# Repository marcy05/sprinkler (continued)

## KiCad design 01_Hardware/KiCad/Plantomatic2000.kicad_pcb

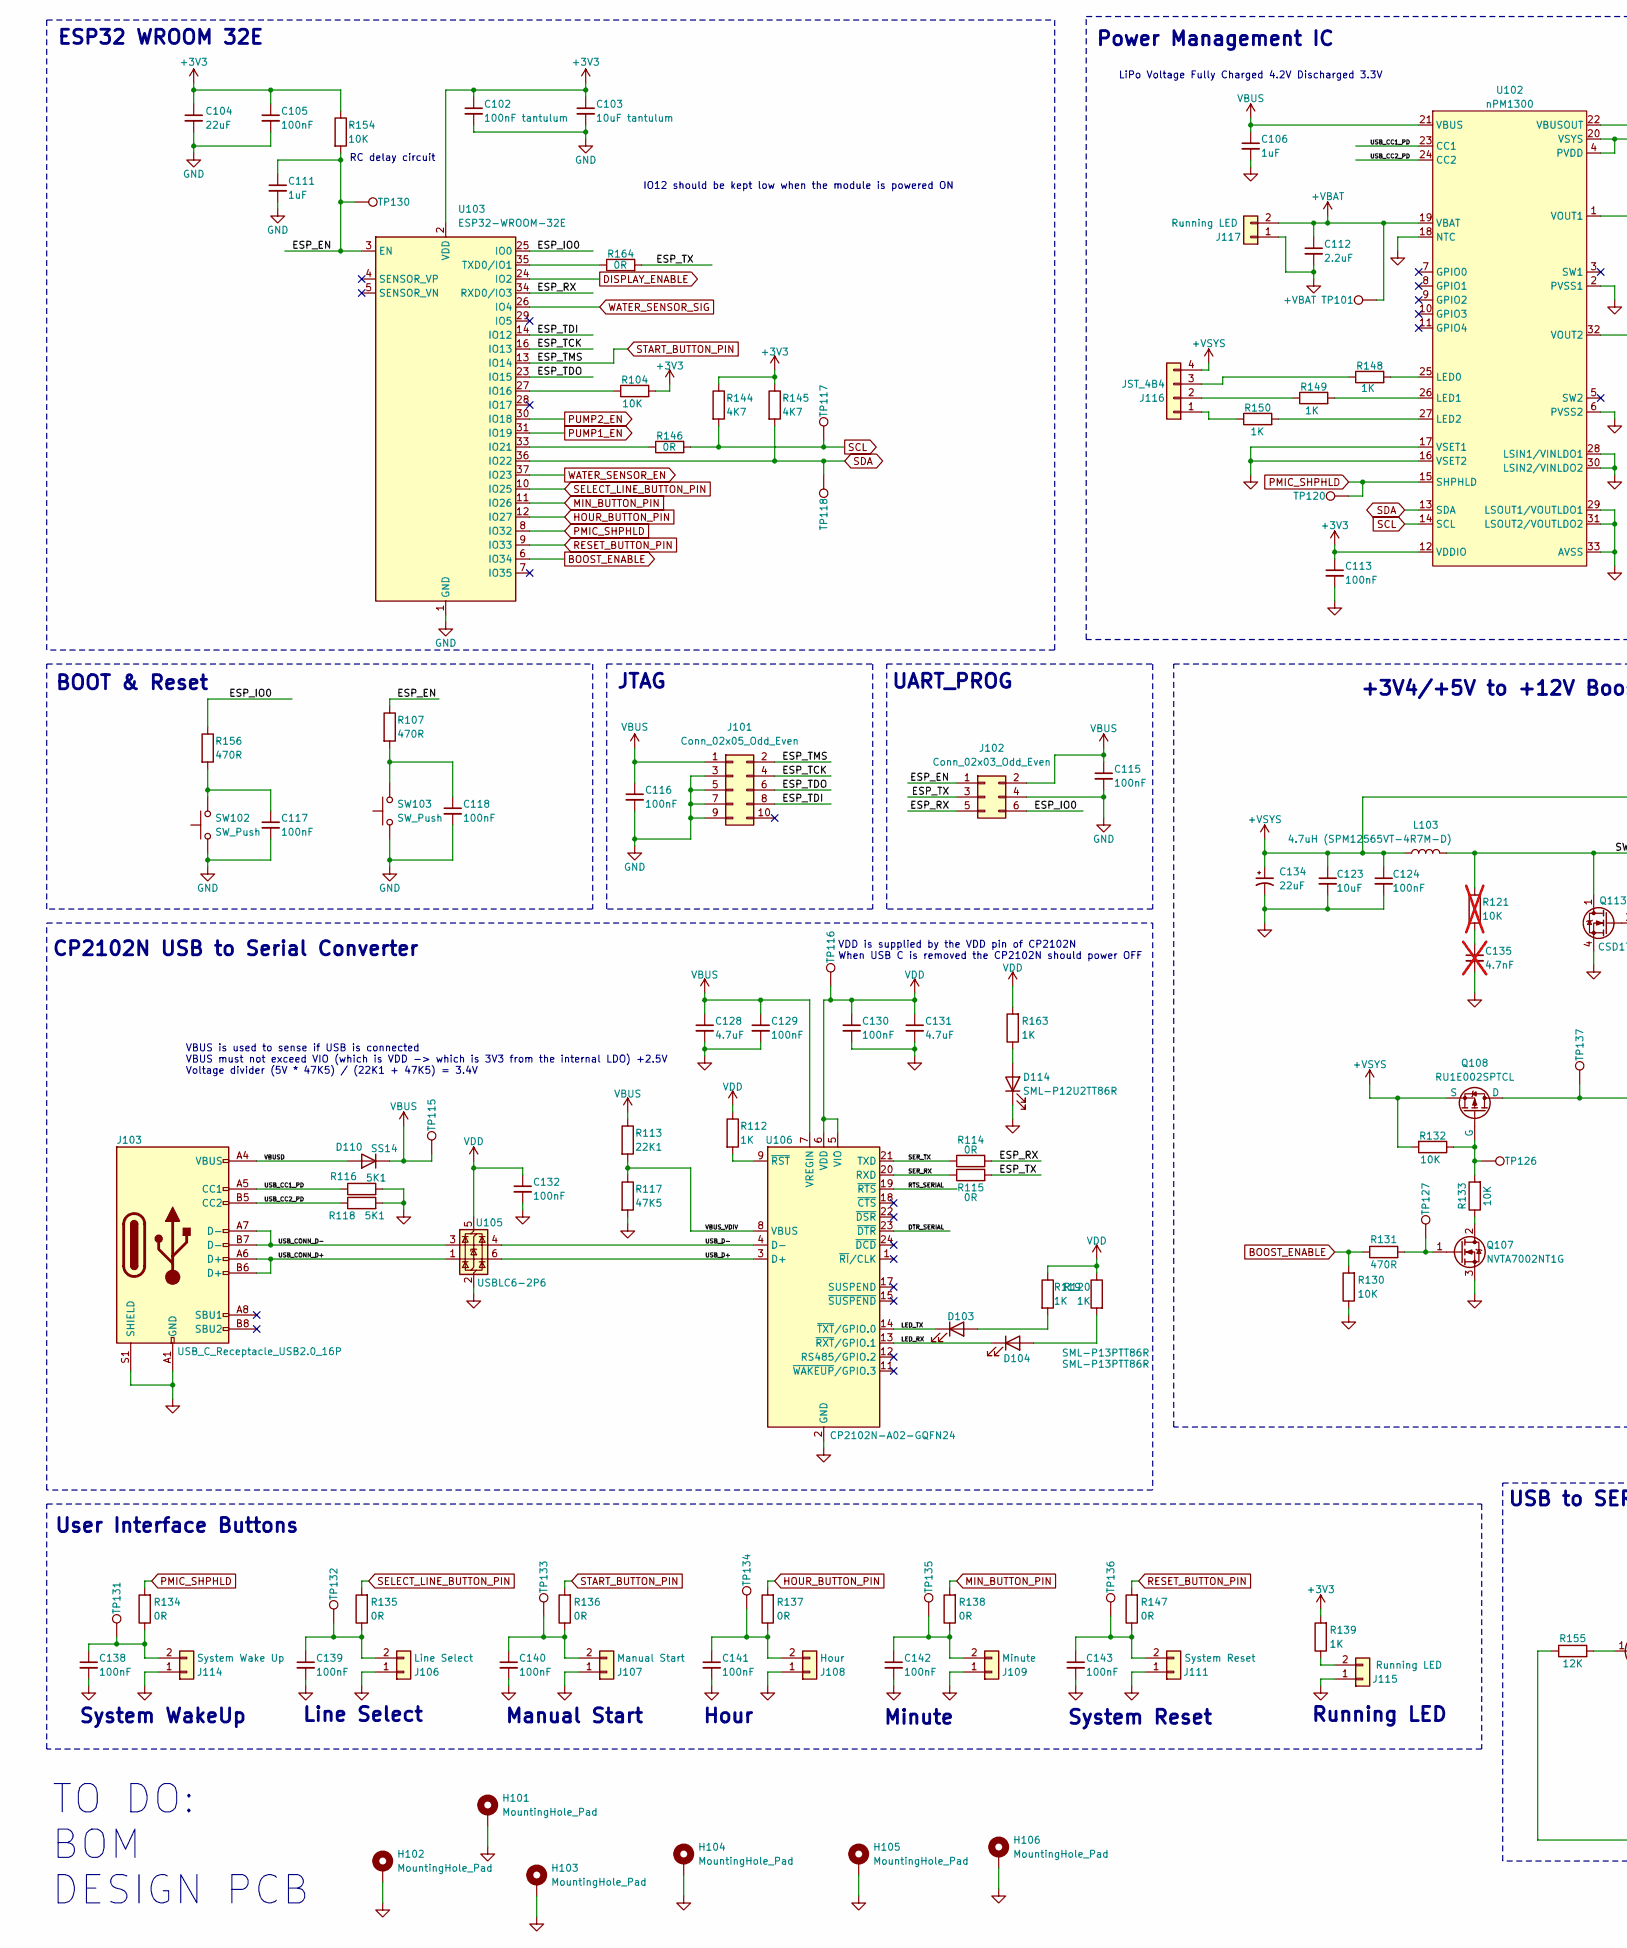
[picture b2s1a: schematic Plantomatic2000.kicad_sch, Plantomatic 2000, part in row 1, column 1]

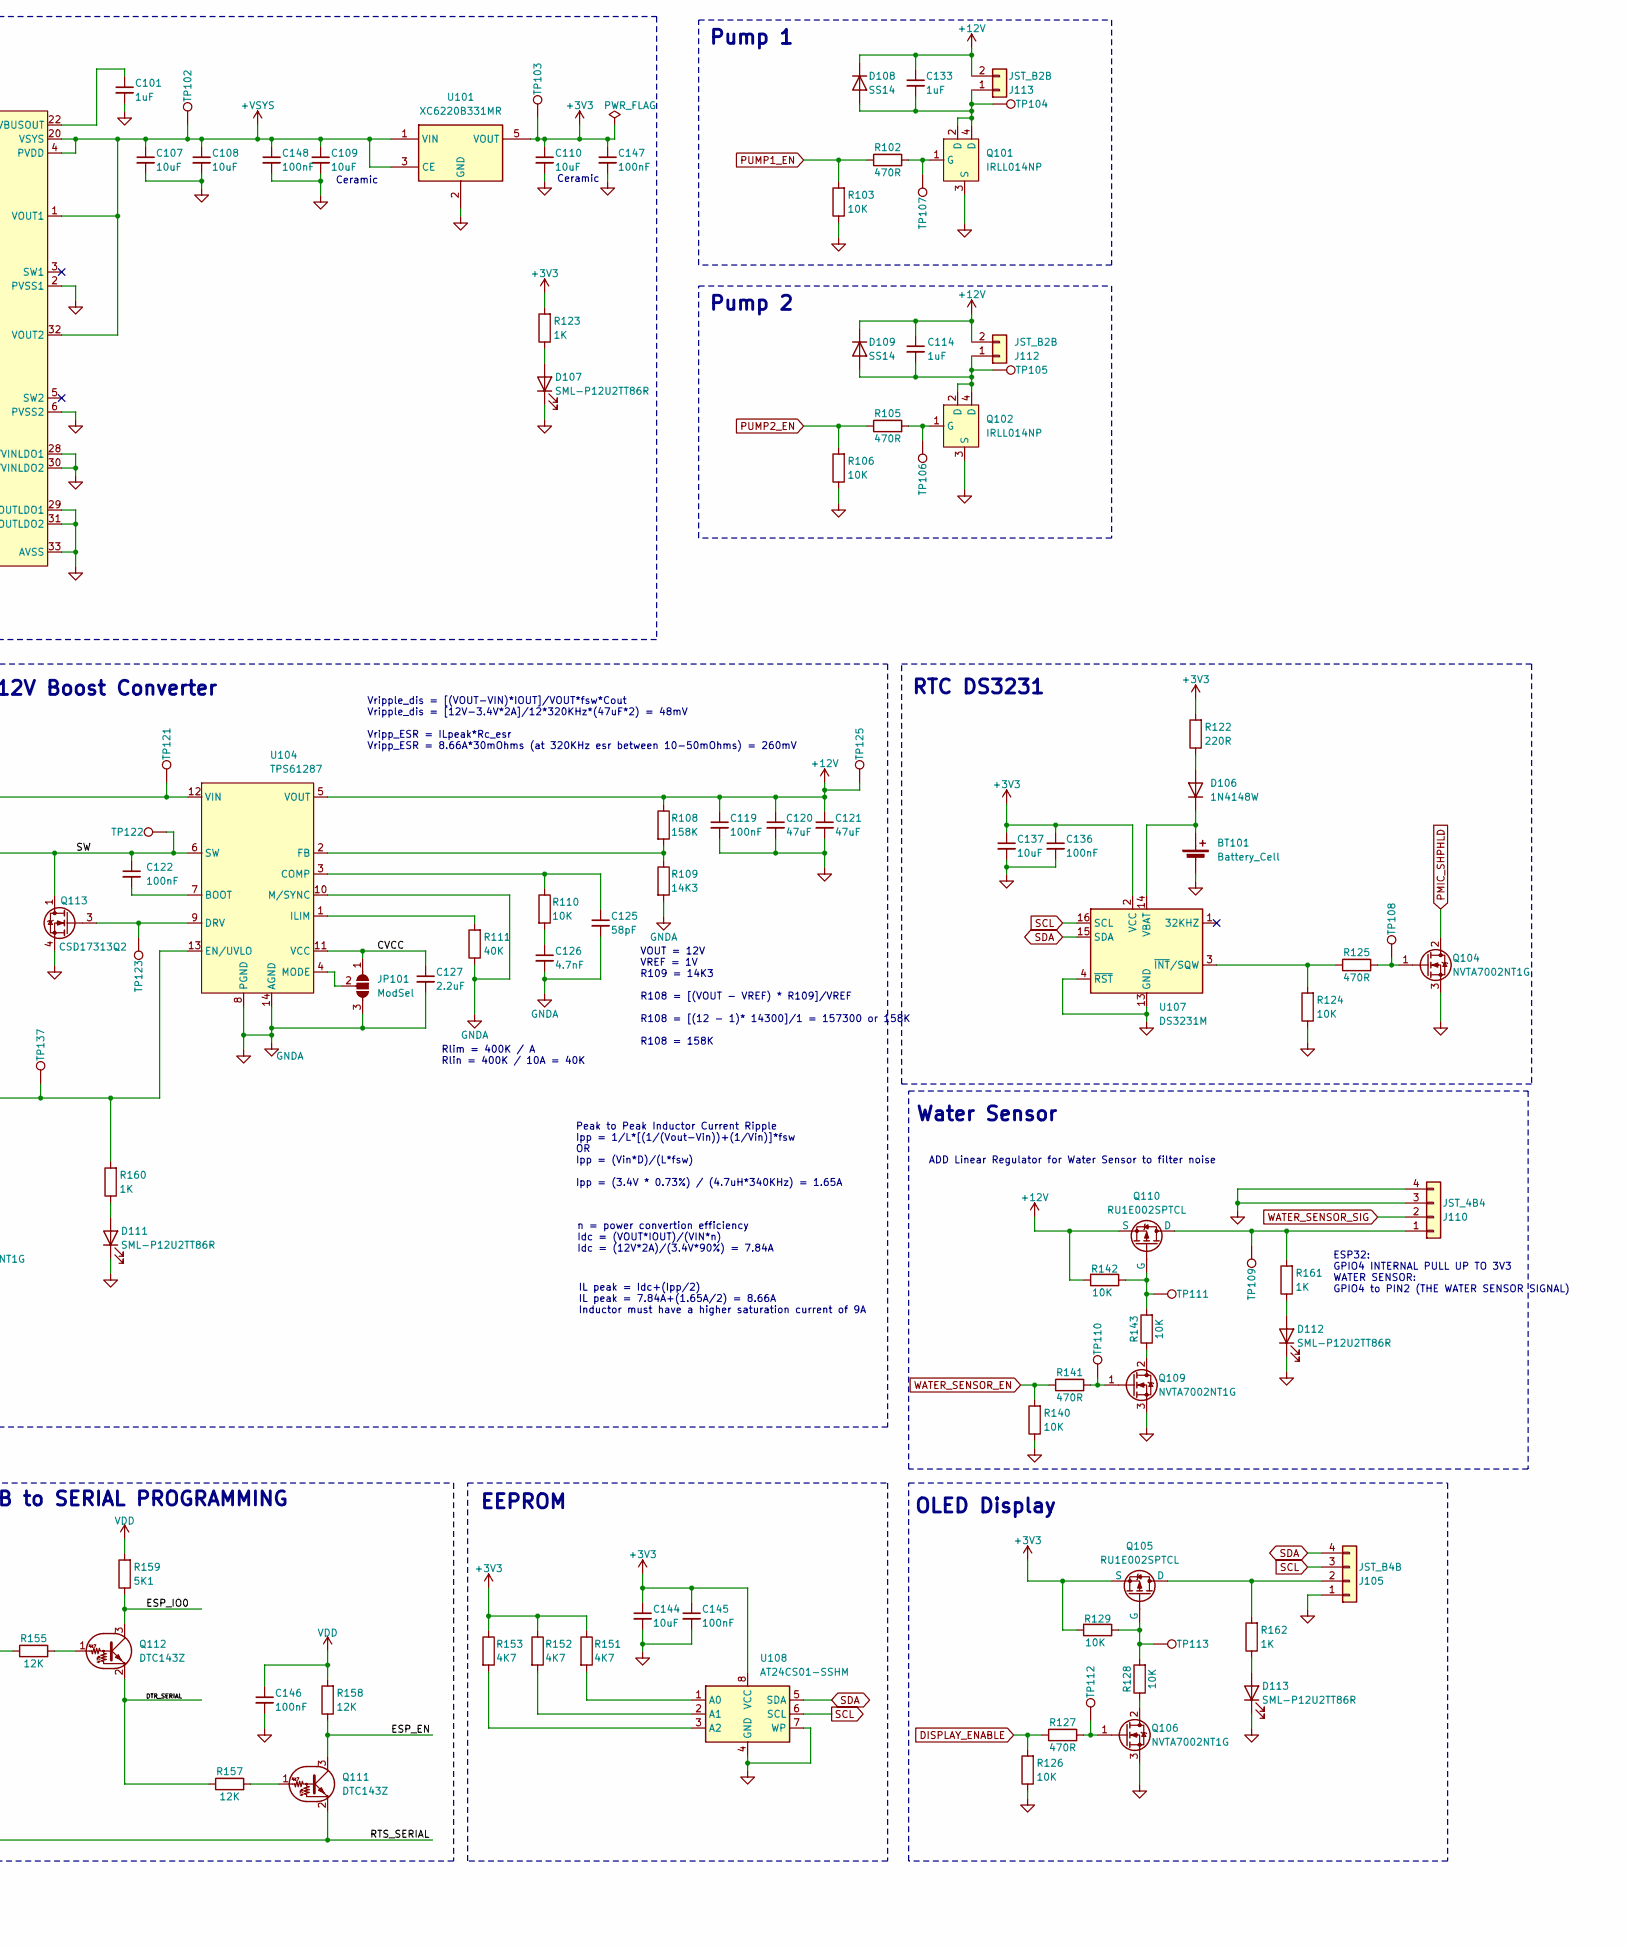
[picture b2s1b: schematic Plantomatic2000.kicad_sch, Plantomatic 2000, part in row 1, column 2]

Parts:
BT101: Battery_Cell; BatteryHolder_MYOUNG_BS-07-A1BJ001_CR2032
C101, C106, C111: 1uF; C_0402_1005Metric
C102: 100nF tantulum; C_1206_3216Metric
C103: 10uF tantulum; C_1206_3216Metric
C104, C134: 22uF; C_0603_1608Metric
C105, C113, C115, C116, C117, C118, C119, C122, C124, C129, C130, C132, C136, C138, C139, C140, C141, C142, C143, C145, C146, C147, C148: 100nF; C_0402_1005Metric
C107, C108, C137, C144: 10uF; C_0402_1005Metric
C109, C110, C123: 10uF; C_0603_1608Metric
C112: 2.2uF; C_0402_1005Metric
C114, C133: 1uF; C_0603_1608Metric
C120, C121: 47uF; C_0603_1608Metric
C125: 58pF; C_0402_1005Metric
C126: 4.7nF; C_0402_1005Metric
C127: 2.2uF; C_0603_1608Metric
C128, C131: 4.7uF; C_0603_1608Metric
C135: 4.7nF; C_0402_1005Metric; not fitted
D103, D104: SML-P13PTT86R; LED_0402_1005Metric
D106: 1N4148W; D_SOD-123
D107, D111, D112, D113, D114: SML-P12U2TT86R; LED_0402_1005Metric
D108, D109, D110: SS14; SS14M_Flyback_Diode
H101, H102, H103, H104, H105, H106: MountingHole_Pad; MountingHole_2.2mm_M2_Pad_TopBottom
J101: Conn_02x05_Odd_Even; PinHeader_2x05_P1.27mm_Vertical_SMD
J102: Conn_02x03_Odd_Even; PinHeader_2x03_P1.27mm_Vertical_SMD
J103: USB_C_Receptacle_USB2.0_16P; USB_C_Receptacle_Palconn_UTC16-G
J105: JST_B4B; JST_EH_B4B-EH-A_1x04_P2.50mm_Vertical
J106: Line Select; JST_EH_B2B-EH-A_1x02_P2.50mm_Vertical
J107: Manual Start; JST_EH_B2B-EH-A_1x02_P2.50mm_Vertical
J108: Hour; JST_EH_B2B-EH-A_1x02_P2.50mm_Vertical
J109: Minute; JST_EH_B2B-EH-A_1x02_P2.50mm_Vertical
J110, J116: JST_4B4; JST_EH_B4B-EH-A_1x04_P2.50mm_Vertical
J111: System Reset; JST_EH_B2B-EH-A_1x02_P2.50mm_Vertical
J112, J113: JST_B2B; JST_EH_B2B-EH-A_1x02_P2.50mm_Vertical
J114: System Wake Up; JST_EH_B2B-EH-A_1x02_P2.50mm_Vertical
J115, J117: Running LED; JST_EH_B2B-EH-A_1x02_P2.50mm_Vertical
JP101: ModSel; SolderJumper-3_P1.3mm_Open_RoundedPad1.0x1.5mm
L103: 4.7uH (SPM12565VT-4R7M-D); SPM12565VT-4R7M
Q101, Q102: IRLL014NP; SOT-223
Q104, Q106, Q107, Q109: NVTA7002NT1G; SOT-323_SC-70
Q105, Q108, Q110: RU1E002SPTCL; SOT-323_SC-70
Q111, Q112: DTC143Z; SOT-23-3
Q113: CSD17313Q2; Texas_DQK
R102, R105, R107, R125, R127, R131, R141, R156: 470R; R_0402_1005Metric
R103, R104, R106, R110, R124, R126, R128, R129, R130, R132, R133, R140, R142, R143, R154: 10K; R_0402_1005Metric
R108: 158K; R_0402_1005Metric
R109: 14K3; R_0402_1005Metric
R111: 40K; R_0402_1005Metric
R112, R119, R120, R123, R139, R148, R149, R150, R160, R161, R162, R163: 1K; R_0402_1005Metric
R113: 22K1; R_0402_1005Metric
R114, R115, R134, R135, R136, R137, R138, R146, R147, R164: 0R; R_0402_1005Metric
R116, R118, R159: 5K1; R_0402_1005Metric
R117: 47K5; R_0402_1005Metric
R121: 10K; R_0402_1005Metric; not fitted
R122: 220R; R_0402_1005Metric
R144, R145, R151, R152, R153: 4K7; R_0402_1005Metric
R155, R157, R158: 12K; R_0402_1005Metric
SW102, SW103: SW_Push; SW_SPST_PTS645
TP101: +VBAT; TestPoint_Pad_D1.0mm
TP102, TP103, TP104, TP105, TP106, TP107, TP108, TP109, TP110, TP111, TP112, TP113, TP115, TP116, TP117, TP118, TP120, TP121, TP122, TP123, TP125, TP126, TP127, TP130, TP131, TP132, TP133, TP134, TP135, TP136, TP137: TestPoint_Pad_D1.0mm
U101: XC6220B331MR; SOT-23-5
U102: nPM1300; QFN-32-1EP_5x5mm_P0.5mm_EP3.6x3.6mm_ThermalVias
U103: ESP32-WROOM-32E
U104: TPS61287; RZP0014A-MFG
U105: USBLC6-2P6; SOT-666
U106: CP2102N-A02-GQFN24; QFN-24-1EP_4x4mm_P0.5mm_EP2.7x2.6mm_ThermalVias
U107: DS3231M; SOIC-16W_7.5x10.3mm_P1.27mm
U108: AT24CS01-SSHM; SOIC-8_3.9x4.9mm_P1.27mm

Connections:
+3V3: C102.1, C103.1, C104.1, C105.1, C110.1, C113.1, C136.1, C137.1, C144.1, C145.1, C147.1, Q105.3 (S), R104.2, R122.2, R123.2, R129.2, R139.2, R144.1, R145.1, R151.1, R152.1, R153.1, R154.1, TP103.1, U101.5 (VOUT), U102.12 (VDDIO), U103.2 (VDD), U107.2 (VCC), U108.8 (VCC)
+12V: C114.1, C119.1, C120.1, C121.1, C133.1, D108.1 (K), D109.1 (K), J112.2, J113.2, Q110.3 (S), R108.1, R142.2, TP125.1, U104.5 (VOUT)
+VBAT: C112.1, J117.2, TP101.1, U102.19 (VBAT)
+VSYS: C107.1, C108.1, C109.1, C123.1, C124.1, C134.1, C148.1, J116.4, L103.2, Q108.3 (S), R132.2, TP102.1, TP121.1, U101.1 (VIN), U101.3 (CE), U102.1 (VOUT1), U102.4 (PVDD), U102.20 (VSYS), U102.32 (VOUT2), U104.12 (VIN)
/CVCC: C127.1, JP101.1 (A), U104.11 (VCC)
/DTR_SERIAL: Q112.2 (E), R157.1, U106.23 (~DTR)
/ESP_EN: C111.1, J102.1, Q111.3 (C), R107.1, R154.2, R158.1, TP130.1, U103.3 (EN)
/ESP_IO0: J102.6, Q112.3 (C), R156.1, R159.1, U103.25 (IO0)
/ESP_RX: J102.5, R114.2, U103.34 (RXD0/IO3)
/ESP_TCK: J101.4, U103.16 (IO13)
/ESP_TDI: J101.8, U103.14 (IO12)
/ESP_TDO: J101.6, U103.23 (IO15)
/ESP_TX: J102.3, R115.2, R164.2
/LED_RX: D104.1 (K), U106.13 (~RXT/GPIO.1)
/LED_TX: D103.1 (K), U106.14 (~TXT/GPIO.0)
/RTS_SERIAL: Q111.2 (E), R155.1, U106.19 (~RTS)
/SER_RX: R115.1, U106.20 (RXD)
/SER_TX: R114.1, U106.21 (TXD)
/SW: C122.1, L103.1, Q113.1 (D), Q113.2 (D), Q113.5 (D), Q113.6 (D), Q113.8 (D), R121.1, TP122.1, U104.6 (SW)
/USB_CC1_PD: J103.A5 (CC1), R116.1, U102.23 (CC1)
/USB_CC2_PD: J103.B5 (CC2), R118.1, U102.24 (CC2)
/USB_CONN_D+: J103.A6 (D+), J103.B6 (D+), U105.1 (I/O1)
/USB_CONN_D-: J103.A7 (D-), J103.B7 (D-), U105.3 (I/O2)
/USB_D+: U105.6 (I/O1), U106.3 (D+)
/USB_D-: U105.4 (I/O2), U106.4 (D-)
/VBUSD: D110.2 (A), J103.A4 (VBUS), J103.A9 (VBUS), J103.B4 (VBUS), J103.B9 (VBUS)
/VBUS_VDIV: R113.2, R117.1, U106.8 (VBUS)
BOOST_ENABLE: R130.2, R131.1, U103.6 (IO34)
DISPLAY_ENABLE: R126.2, R127.1, U103.24 (IO2)
GND: BT101.2 (-), C101.2, C102.2, C103.2, C104.2, C105.2, C106.2, C107.2, C108.2, C109.2, C110.2, C111.2, C112.2, C113.2, C115.2, C116.2, C117.2, C118.2, C119.2, C120.2, C121.2, C123.2, C124.2, C125.2, C126.2, C127.2, C128.2, C129.2, C130.2, C131.2, C132.2, C134.2, C135.2, C136.2, C137.2, C138.2, C139.2, C140.2, C141.2, C142.2, C143.2, C144.2, C145.2, C146.2, C147.2, C148.2, D107.1 (K), D111.1 (K), D112.1 (K), D113.1 (K), D114.1 (K), H101.1, H102.1, H103.1, H104.1, H105.1, H106.1, J101.3, J101.5, J101.7, J101.9, J102.4, J103.A1 (GND), J103.A12 (GND), J103.B1 (GND), J103.B12 (GND), J103.S1 (SHIELD), J105.1, J106.1, J107.1, J108.1, J109.1, J110.3, J110.4, J111.1, J114.1, J115.1, J117.1, JP101.3 (B), Q101.3 (S), Q102.3 (S), Q104.3 (S), Q106.3 (S), Q107.3 (S), Q109.3 (S), Q113.4 (S), Q113.7 (S), R103.1, R106.1, R109.2, R111.1, R116.2, R117.2, R118.2, R124.1, R126.1, R130.1, R140.1, SW102.1, SW103.1, U101.2 (GND), U102.2 (PVSS1), U102.6 (PVSS2), U102.16 (VSET2), U102.17 (VSET1), U102.18 (NTC), U102.28 (LSIN1/VINLDO1), U102.29 (LSOUT1/VOUTLDO1), U102.30 (LSIN2/VINLDO2), U102.31 (LSOUT2/VOUTLDO2), U102.33 (AVSS), U103.1 (GND), U103.15 (GND), U103.38 (GND), U103.39 (GND), U104.8 (PGND), U104.10 (M/SYNC), U104.14 (AGND), U105.2 (GND), U106.2 (GND), U106.25 (GND), U107.4 (~RST), U107.5 (GND), U107.6 (GND), U107.7 (GND), U107.8 (GND), U107.9 (GND), U107.10 (GND), U107.11 (GND), U107.12 (GND), U107.13 (GND), U108.4 (GND), U108.7 (WP)
HOUR_BUTTON_PIN: R137.2, U103.12 (IO27)
MIN_BUTTON_PIN: R138.2, U103.11 (IO26)
unnamed: BT101.1 (+), D106.1 (K), U107.14 (VBAT)
unnamed: C117.1, R156.2, SW102.2
unnamed: C118.1, R107.2, SW103.2
unnamed: C126.1, R110.2
unnamed: C135.1, R121.2
unnamed: D103.2 (A), R119.2
unnamed: D104.2 (A), R120.2
unnamed: D106.2 (A), R122.1
unnamed: D107.2 (A), R123.1
unnamed: C133.2, D108.2 (A), J113.1, Q101.2 (D), Q101.4 (D), TP104.1
unnamed: C114.2, D109.2 (A), J112.1, Q102.2 (D), Q102.4 (D), TP105.1
unnamed: D111.2 (A), R160.1
unnamed: D112.2 (A), R161.1
unnamed: D113.2 (A), R162.1
unnamed: D114.2 (A), R163.1
unnamed: J105.2, Q105.1 (D), R162.2
unnamed: C139.1, J106.2, R135.1, TP132.1
unnamed: C140.1, J107.2, R136.1, TP133.1
unnamed: C141.1, J108.2, R137.1, TP134.1
unnamed: C142.1, J109.2, R138.1, TP135.1
unnamed: J110.1, Q110.1 (D), R161.2, TP109.1
unnamed: C143.1, J111.2, R147.1, TP136.1
unnamed: C138.1, J114.2, R134.1, TP131.1
unnamed: J115.2, R139.1
unnamed: J116.1, R150.1
unnamed: J116.2, R149.1
unnamed: J116.3, R148.1
unnamed: JP101.2 (C), U104.4 (MODE)
unnamed: Q101.1 (G), R102.2, TP107.1
unnamed: Q102.1 (G), R105.2, TP106.1
unnamed: Q104.1 (G), R125.2, TP108.1
unnamed: Q105.2 (G), R128.2, R129.1, TP113.1
unnamed: Q106.2 (D), R128.1
unnamed: Q106.1 (G), R127.2, TP112.1
unnamed: Q107.2 (D), R133.1
unnamed: Q107.1 (G), R131.2, TP127.1
unnamed: Q108.1 (D), R160.2, TP137.1, U104.13 (EN/UVLO)
unnamed: Q108.2 (G), R132.1, R133.2, TP126.1
unnamed: Q109.2 (D), R143.1
unnamed: Q109.1 (G), R141.2, TP110.1
unnamed: Q110.2 (G), R142.1, R143.2, TP111.1
unnamed: Q111.1 (B), R157.2
unnamed: Q112.1 (B), R155.2
unnamed: Q113.3 (G), TP123.1, U104.9 (DRV)
unnamed: R148.2, U102.25 (LED0)
unnamed: R149.2, U102.26 (LED1)
unnamed: R150.2, U102.27 (LED2)
unnamed: C101.1, U102.22 (VBUSOUT)
unnamed: R104.1, U103.27 (IO16)
unnamed: R146.1, U103.33 (IO21)
unnamed: R164.1, U103.35 (TXD0/IO1)
unnamed: C122.2, U104.7 (BOOT)
unnamed: C125.1, R110.1, U104.3 (COMP)
unnamed: R108.2, R109.1, U104.2 (FB)
unnamed: R111.2, U104.1 (ILIM)
unnamed: R112.2, U106.9 (~RST)
unnamed: R124.2, R125.1, U107.3 (~INT/SQW)
unnamed: R151.2, U108.1 (A0)
unnamed: R152.2, U108.2 (A1)
unnamed: R153.2, U108.3 (A2)
PMIC_SHPHLD: Q104.2 (D), R134.2, TP120.1, U102.15 (SHPHLD), U103.8 (IO32)
PUMP1_EN: R102.1, R103.2, U103.31 (IO19)
PUMP2_EN: R105.1, R106.2, U103.30 (IO18)
RESET_BUTTON_PIN: R147.2, U103.9 (IO33)
SCL: J105.3, R144.2, R146.2, TP117.1, U102.14 (SCL), U107.16 (SCL), U108.6 (SCL)
SDA: J105.4, R145.2, TP118.1, U102.13 (SDA), U103.36 (IO22), U107.15 (SDA), U108.5 (SDA)
SELECT_LINE_BUTTON_PIN: R135.2, U103.10 (IO25)
START_BUTTON_PIN: J101.2, R136.2, U103.13 (IO14)
VBUS: C106.1, C115.1, C116.1, C128.1, C129.1, D110.1 (K), J101.1, J102.2, R113.1, TP115.1, U102.21 (VBUS), U106.7 (VREGIN)
VDD: C130.1, C131.1, C132.1, C146.1, R112.1, R119.1, R120.1, R158.2, R159.2, R163.2, TP116.1, U105.5 (VBUS), U106.5 (VIO), U106.6 (VDD)
WATER_SENSOR_EN: R140.2, R141.1, U103.37 (IO23)
WATER_SENSOR_SIG: J110.2, U103.26 (IO4)

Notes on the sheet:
VBUS is used to sense if USB is connected VBUS must not exceed VIO (which is VDD -> which is 3V3 from the internal LDO) +2.5V Voltage divider (5V * 47K5) / (22K1 + 47K5) = 3.4V
Water Sensor
VOUT = 12V VREF = 1V R109 = 14K3 R108 = [(VOUT - VREF) * R109]/VREF R108 = [(12 - 1)* 14300]/1 = 157300 or 158K R108 = 158K
RTC DS3231
USB to SERIAL PROGRAMMING
User Interface Buttons
Power Management IC
OLED Display
EEPROM
Peak to Peak Inductor Current Ripple Ipp = 1/L*[(1/(Vout-Vin))+(1/Vin)]*fsw OR Ipp = (Vin*D)/(L*fsw) Ipp = (3.4V * 0.73%) / (4.7uH*340KHz) = 1.65A
BOOT & Reset
ESP32 WROOM 32E
ADD Linear Regulator for Water Sensor to filter noise
Manual Start
n = power convertion efficiency Idc = (VOUT*IOUT)/(VIN*n) Idc = (12V*2A)/(3.4V*90%) = 7.84A
JTAG
Ceramic
IL peak = Idc+(Ipp/2) IL peak = 7.84A+(1.65A/2) = 8.66A Inductor must have a higher saturation current of 9A
CP2102N USB to Serial Converter
System WakeUp
IO12 should be kept low when the module is powered ON
System Reset
TO DO: BOM DESIGN PCB
Pump 1
Minute
Pump 2
Vripple_dis = [(VOUT-VIN)*IOUT]/VOUT*fsw*Cout Vripple_dis = [12V-3.4V*2A]/12*320KHz*(47uF*2) = 48mV Vripp_ESR = ILpeak*Rc_esr Vripp_ESR = 8.66A*30mOhms (at 320KHz esr between 10-50mOhms) = 260mV
RC delay circuit
ESP32: GPIO4 INTERNAL PULL UP TO 3V3 WATER SENSOR: GPIO4 to PIN2 (THE WATER SENSOR SIGNAL)
Running LED
LiPo Voltage Fully Charged 4.2V Discharged 3.3V
UART_PROG
Hour
+3V4/+5V to +12V Boost Converter
Rlim = 400K / A Rlin = 400K / 10A = 40K
Line Select
VDD is supplied by the VDD pin of CP2102N When USB C is removed the CP2102N should power OFF

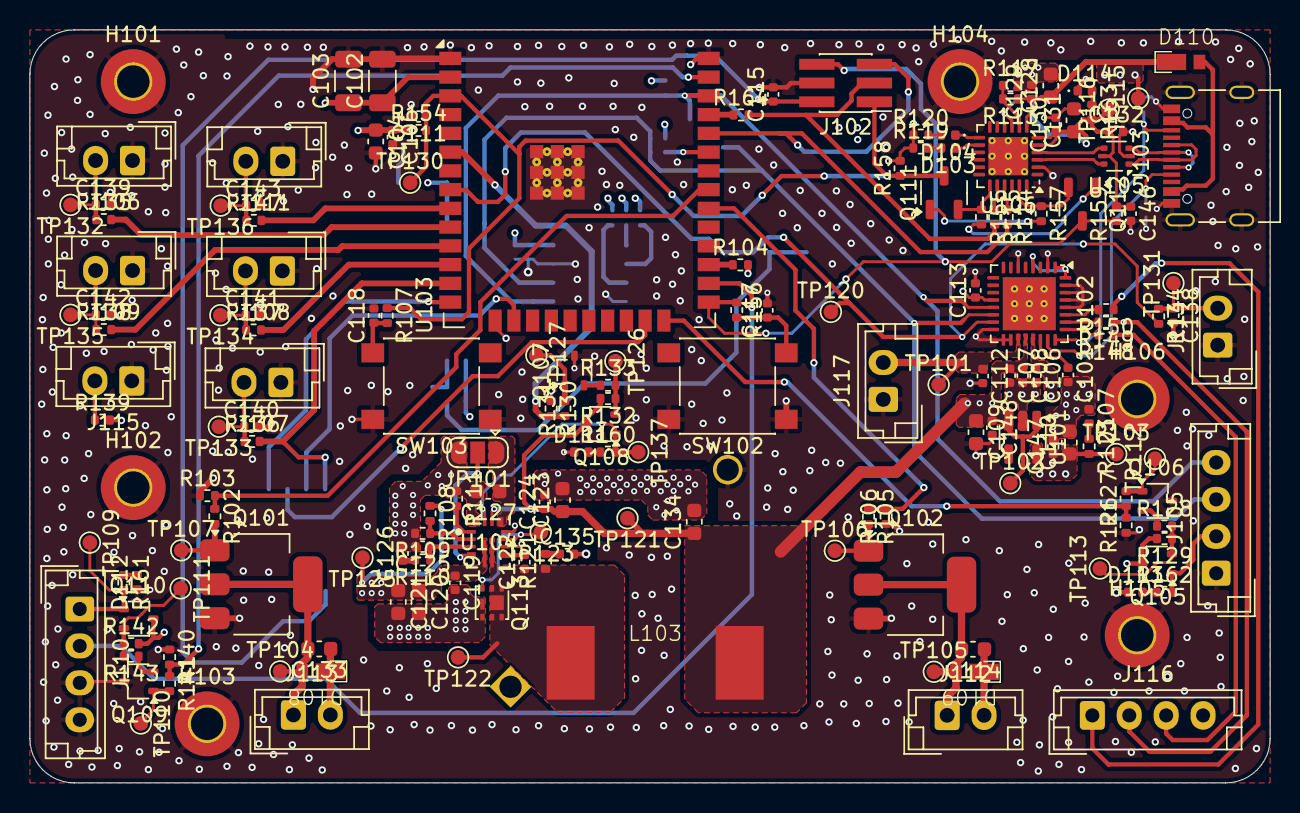
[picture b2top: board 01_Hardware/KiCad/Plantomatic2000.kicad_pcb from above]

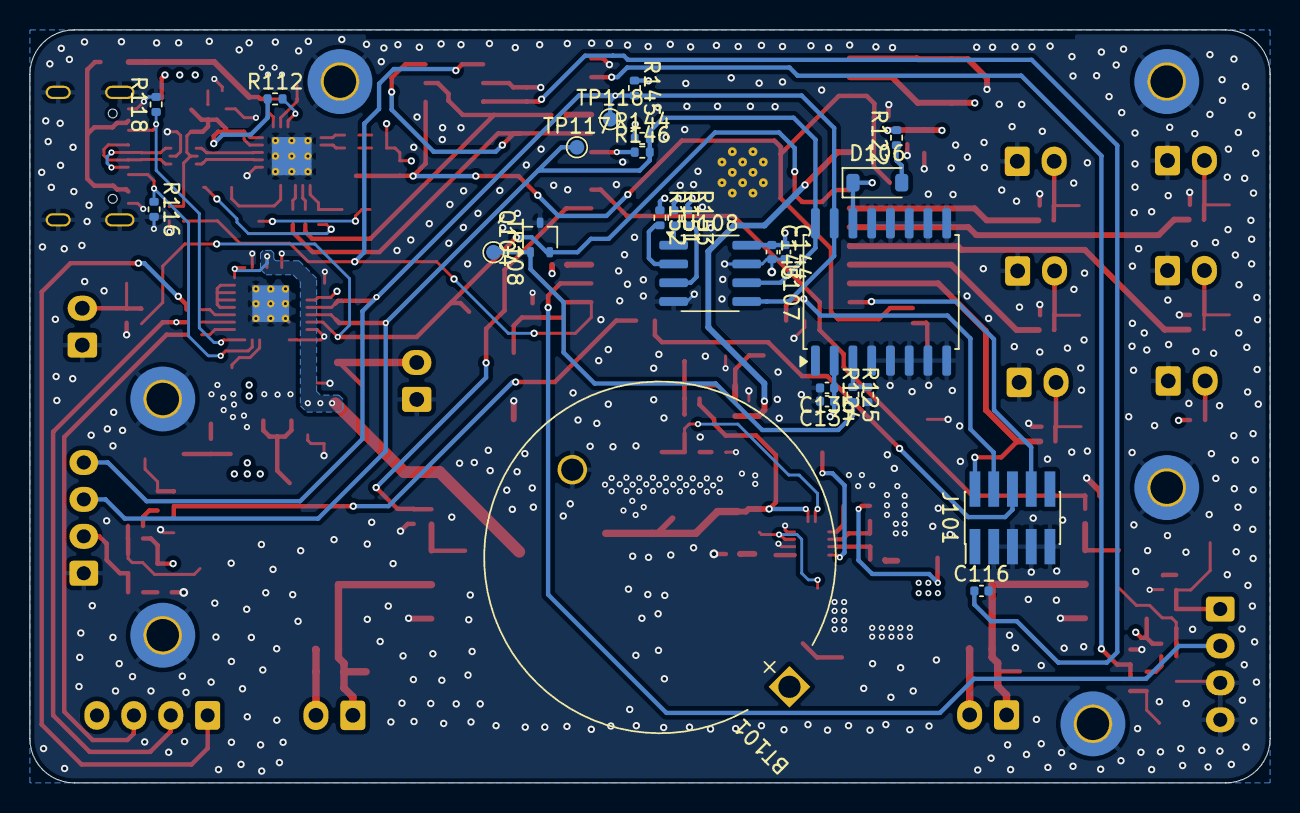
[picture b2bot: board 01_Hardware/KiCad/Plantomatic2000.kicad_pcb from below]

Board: 4 copper layers, 84.0 x 51.0 mm, 201 parts (26 on the bottom side), 104 nets.

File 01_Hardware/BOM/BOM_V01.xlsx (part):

Reference | Qty | PCB Quantity | Ordered | Description | Value | Footprint | Manufacturer | Manufacturer Part Number | Part Link
BT101 | 1 | 5 |  |  | Battery_Cell | Battery:BatteryHolder_MYOUNG_BS-07-A1BJ001_CR2032
C101,C106,C111 | 3 | 15 | 100 |  | 1uF | Capacitor_SMD:C_0402_1005Metric | Murata | GXT155R61A105KE01D | https://www.mouser.it/ProductDetail/Murata-Electronics/GXT15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
C102 | 1 | 5 | 10 |  | 100nF tantulum → 1uF | Capacitor_SMD:C_1206_3216Metric | Yageo | T491A105K025AT7280 | https://www.mouser.it/ProductDetail/KEMET/T491A105K025AT7280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
C103 | 1 | 5 | 6 |  | 10uF tantulum | Capacitor_SMD:C_1206_3216Metric | Yageo | T491A106K016AT7280 | https://www.mouser.it/ProductDetail/KEMET/T491A106K016AT7280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
C104,C134 | 2 | 10 | 12 |  | 22uF | Capacitor_SMD:C_0603_1608Metric | Murata | GRM188C61C226ME01D | https://www.mouser.it/ProductDetail/Murata-Electronics/GRM18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
C105,C113,C115,C116,C117,C118,C119,C122,C124,C129,C130,C132,C136,C138,C139,C140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 | 23 | 115 | 220 |  | 100nF | Capacitor_SMD:C_0402_1005Metric | Murata | GCM155R71H104KE02D | https://www.mouser.it/ProductDetail/Murata-Electronics/GCM15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
C107,C108,C137,C144 | 4 | 20 | 22 |  | 10uF | Capacitor_SMD:C_0402_1005Metric | Murata | GRT155R61A106ME13D | https://www.mouser.it/ProductDetail/Murata-Electronics/GRT15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
C109,C110,C123 | 3 | 15 | 20 |  | 10uF | Capacitor_SMD:C_0603_1608Metric | Murata | GRM188R61E106KA73D | https://www.mouser.it/ProductDetail/Murata-Electronics/GRM18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
C112 | 1 | 5 | 10 |  | 2.2uF | Capacitor_SMD:C_0402_1005Metric | Murata | GRM155C71A225KE11J | https://www.mouser.it/ProductDetail/Murata-Electronics/GRM15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
C114,C133 | 2 | 10 | 12 |  | 1uF | Capacitor_SMD:C_0603_1608Metric | Murata | GCM188D71H105KE36W | https://www.mouser.it/ProductDetail/Murata-Electronics/GCM18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
C120,C121 | 2 | 10 | 14 |  | 47uF | Capacitor_SMD:C_1206_1608Metric | Murata | GRM31CR61C476ME44L | https://www.mouser.it/ProductDetail/Murata-Electronics/GRM31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
C120,C121 | 2 | 10 | 14 |  | 22uF | Capacitor_SMD:C_0805_1608Metric | Kyocera AVX | 08054D226MAT2A | https://www.mouser.it/ProductDetail/KYOCERA-AVX/08054D226MAT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
C125 | 1 | 5 | 6 |  | 58pF | Capacitor_SMD:C_0402_1005Metric | Kyocera AVX | 04025A560KAT2A | https://www.mouser.it/ProductDetail/KYOCERA-AVX/04025A560KAT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
C126 | 1 | 5 | 100 |  | 4.7nF | Capacitor_SMD:C_0402_1005Metric | Murata | GCM155R71H472KA37J | https://www.mouser.it/ProductDetail/Murata-Electronics/GCM15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
C127 | 1 | 5 | 30 |  | 2.2uF | Capacitor_SMD:C_0603_1608Metric | Murata | GRM188C81C225KA12D | https://www.mouser.it/ProductDetail/Murata-Electronics/GRM18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
C128,C131 | 2 | 10 | 20 |  | 4.7uF | Capacitor_SMD:C_0603_1608Metric | Murata | GRM188R61E475KE11D | https://www.mouser.it/ProductDetail/Murata-Electronics/GRM18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
C135 | 1 | 5 |  | Snubbing DNP | 4.7nF | Capacitor_SMD:C_0402_1005Metric
D106 | 1 | 5 | 10 |  | 1N4148W | Diode_SMD:D_SOD-123 | Diotec Semiconductor | 1N4148W | https://www.mouser.it/ProductDetail/Diotec-Semiconductor/1N4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
D107,D111,D112,D113,D114,D103,D104 | 7 | 35 | 40 |  | SML-P12U2TT86R | LED_SMD:LED_0402_1005Metric | ROHM Semiconductor | SML-P12U2TT86R | https://www.mouser.it/ProductDetail/ROHM-Semiconductor/SML-P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
D108,D109,D110 | 3 | 15 | 20 |  | SS14M | Custom_Global_Footprints:SS14M_Flyback_Diode | Taiwan Semiconductor | SS14M | https://www.mouser.it/ProductDetail/Taiwan-Semiconductor/SS1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
J101 | 1 | 5 |  |  | Conn_02x05_Odd_Even | Connector_PinHeader_1.27mm:PinHeader_2x05_P1.27mm_Vertical_SMD
J102 | 1 | 5 |  |  | Conn_02x03_Odd_Even | Connector_PinHeader_1.27mm:PinHeader_2x03_P1.27mm_Vertical_SMD
J103 | 1 | 5 | 6 |  | USB_C_Receptacle_USB2.0_16P | Connector_USB:USB_C_Receptacle_Palconn_UTC16-G | Molex | 217179-0001 | https://www.mouser.it/ProductDetail/Molex/217179-0001?qs=DRk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
J105, J110,J116 | 3 | 15 |  |  | JST_B4B | Connector_JST:JST_EH_B4B-EH-A_1x04_P2.50mm_Vertical
J112,J113, J114, J106, J107, J108, J109, J111, J115, J117 | 10 | 50 |  |  | JST_B2B | Connector_JST:JST_EH_B2B-EH-A_1x02_P2.50mm_Vertical
L103 | 1 | 5 | 5 |  | 4.7uH (SPM12565VT-4R7M-D) | Custom_Global_Footprints:SPM12565VT-4R7M | TDK | SPM12565VT-4R7M-D | https://www.mouser.it/ProductDetail/TDK/SPM12565VT-4R7M-D?qs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
Q101,Q102 | 2 | . | 12 |  | STN3NF06L | Package_TO_SOT_SMD:SOT-223 | STMicroelectronics | STN3NF06L | https://www.mouser.it/ProductDetail/STMicroelectronics/STN3N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
Q104,Q106,Q107,Q109 | 4 | 20 | 40 |  | NVTA7002NT1G | Package_TO_SOT_SMD:SOT-323_SC-70 | Onsemi | NVTA7002NT1G | https://www.mouser.it/ProductDetail/onsemi/NVTA7002NT1G?qs=3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
Q105,Q108,Q110 | 3 | 15 | 30 |  | RU1E002SPTCL | Package_TO_SOT_SMD:SOT-323_SC-70 | ROHM Semiconductor | RU1E002SPTCL | https://www.mouser.it/ProductDetail/ROHM-Semiconductor/RU1E0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
Q111,Q112 | 2 | 10 | 30 |  | DTC143Z | Package_TO_SOT_SMD:SOT-23-3 | Nexperia | PDTC143ZT,215 | https://www.mouser.it/ProductDetail/Nexperia/PDTC143ZT215?qs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
Q113 | 1 | 5 | 10 |  | CSD17313Q2 | Package_SON:Texas_DQK | Texas Instruments | CSD17313Q2 | https://www.mouser.it/ProductDetail/Texas-Instruments/CSD173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
R102,R105,R107,R125,R127,R131,R141,R156 | 8 | 40 | 50 |  | 470R | Resistor_SMD:R_0402_1005Metric | Vishay | CRCW0402470RFKEDHP | https://www.mouser.it/ProductDetail/Vishay/CRCW0402470RFKEDH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
R103,R104,R106,R110,R124,R126,R128,R129,R130,R132,R133,R140,R142,R143,R154 | 15 | 75 | 100 |  | 10K | Resistor_SMD:R_0402_1005Metric | Vishay | CRCW040210K0FKEDHP | https://www.mouser.it/ProductDetail/Vishay/CRCW040210K0FKEDH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
R108 | 1 | 5 | 7 |  | 158K | Resistor_SMD:R_0402_1005Metric | Yageo | RE0402BRE07158KL | https://www.mouser.it/ProductDetail/YAGEO/RE0402BRE07158KL?q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
R109 | 1 | 5 | 100 |  | 14K3 | Resistor_SMD:R_0402_1005Metric | Yageo | AC0402FR-0714K3L | https://www.mouser.it/ProductDetail/YAGEO/AC0402FR-0714K3L?q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
R111 | 1 | 5 | 60 |  | 40K2 | Resistor_SMD:R_0402_1005Metric | Bourns | CR0402-FX-4022GLF | https://www.mouser.it/ProductDetail/Bourns/CR0402-FX-4022GLF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
R112,R119,R120,R123,R139,R148,R149,R150,R160,R161,R162,R163 | 12 | 60 | 100 |  | 1K | Resistor_SMD:R_0402_1005Metric | Vishay | MCS04020C1001FE000 | https://www.mouser.it/ProductDetail/Vishay-Beyschlag/MCS0402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
R113 | 1 | 5 | 100 |  | 22K1 | Resistor_SMD:R_0402_1005Metric | Bourns | CR0402-FX-2212GLF | https://www.mouser.it/ProductDetail/Bourns/CR0402-FX-2212GLF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
R114,R115,R134,R135,R136,R137,R138,R146,R147,R164 | 10 | 50 | 200 |  | 0R | Resistor_SMD:R_0402_1005Metric | Vishay | CRCW04020000Z0EDC | https://www.mouser.it/ProductDetail/Vishay/CRCW04020000Z0EDC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
R116,R118,R159 | 3 | 15 | 30 |  | 5K1 | Resistor_SMD:R_0402_1005Metric | Vishay | MCS04020D5101BE000 | https://www.mouser.it/ProductDetail/Vishay-Beyschlag/MCS0402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
R117 | 1 | 5 | 30 |  | 47K5 | Resistor_SMD:R_0402_1005Metric | Vishay | CRCW040247K5FKED | https://www.mouser.it/ProductDetail/Vishay/CRCW040247K5FKED?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
R121 | 1 | 5 |  | Snubbing DNP | 10K | Resistor_SMD:R_0402_1005Metric
R122 | 1 | 5 | 20 |  | 220R | Resistor_SMD:R_0402_1005Metric | Vishay | RCS0402220RFKED | https://www.mouser.it/ProductDetail/Vishay-Draloric/RCS04022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
R144,R145,R151,R152,R153 | 5 | 25 | 100 |  | 4K7 | Resistor_SMD:R_0402_1005Metric | Vishay | RCS04024K70FKED | https://www.mouser.it/ProductDetail/Vishay-Draloric/RCS04024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
R155,R157,R158 | 3 | 15 | 20 |  | 12K | Resistor_SMD:R_0402_1005Metric | Vishay | RCS040212K0FKED | https://www.mouser.it/ProductDetail/Vishay-Draloric/RCS04021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
SW102,SW103 | 2 | 10 | 12 |  | SW_Push | Button_Switch_SMD:SW_SPST_PTS645 | Same Sky | TS04-66-85-BK-160-SMT | https://www.mouser.it/ProductDetail/Same-Sky/TS04-66-85-BK-1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
U101 | 1 | 5 | 5 |  | XC6220B331MR | Package_TO_SOT_SMD:SOT-23-5 | Torex Semiconductor | XC6220B331MR-G | https://www.mouser.it/ProductDetail/Torex-Semiconductor/XC62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
U102 | 1 | 5 | 5 |  | nPM1300 | Package_DFN_QFN:QFN-32-1EP_5x5mm_P0.5mm_EP3.6x3.6mm_ThermalVias | Nordic Semiconductor | nPM1300-QEAA-R7 | https://www.mouser.it/ProductDetail/Nordic-Semiconductor/nPM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

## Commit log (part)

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2025-03-16 Add basic project information and structure
2025-03-19 Initialized platformIO development
2025-03-19 Included library folder
2025-03-19 Included custom library folder
2025-03-19 Add serial speed
2025-03-27 Add documentation, datasheet and diagram
2025-03-27 Add ESP32 datasheet
2025-03-29 Removed backup file from tracking
2025-03-29 ESP32 datasheet and releated documents
2025-03-29 Working Deep sleep, led, reset button, wakeup, compilation environments
2025-03-29 Added system flow chart
2025-03-29 Excluded backup files
2025-03-31 Add logger
2025-04-01 Add WiFi connection handling
2025-04-01 Grouped build environment
2025-04-01 Add upper bound to the password and ssid length
2025-04-01 Add variable to manage the deepsleepwakeup in the timer class
2025-04-01 Add mDNS to connect more easily to the setting page for wifi
2025-04-12 Excluded NoShare folder
2025-05-06 removed WiFi part from the project
2025-05-06 Removed WiFi led and WiFi manager
2025-05-06 Moved battery pin next to run
2025-05-06 Add working display
2025-05-10 Add pump selector button and display code
2025-05-10 Add restart function to reset button
2025-05-10 Shifted one line down the pumps
2025-05-10 Overall display setting and GPIO config
2025-05-11 Add working RTC time
2025-05-11 Fixed Pin assignment
2025-05-11 Add selection for Time line
2025-05-11 Current time shown correctly
2025-05-14 Renamed lib to uniform naming
2025-05-14 Introduced pump timers
2025-05-17 Add pump timers
2025-05-17 Add fix daily_timer
2025-05-17 Add deep spleep screen
2025-05-17 Cleaned the main loop
2025-05-17 Hardware sync
2025-05-18 Sprinkler schematic, some datasheets and PDN block diagram (all of then need updates)
2025-05-18 Test commit
2025-05-22 Update diagrams and HW readme
2025-05-22 Add Timer activation support
2025-05-22 Cleaned code and improved logging
2025-05-24 Schematic: Added TPS61287 +12V Boost converter, Datasheet: TPS61287 and preliminary BOM
2025-05-24 Updated README_Hardware doc with quick -next, steps-
2025-05-24 Added DS3231 RTC + datasheets with interuppt wake up from RTC to nPM1300 PMIC
2025-05-25 Schematic: Added enable circuitry for Display, Water Sensor and Boost converter. Also connectors, LED's, EEPROM, USB to Serial Programming (RTS and DTR). Added datasheets and simulation of Enable cir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
2025-06-01 Aligned GPIOs and logic
2025-06-01 Used the RTC alarm to sleep and wakeup the system
2025-06-01 Setup RTC alarms and sleep handling
2025-06-01 Added foorptrints
2025-06-02 Finised assigning footprints
2025-06-02 Added test points and schematic.pdf file
2025-06-02 main loop splitted in functions
2025-06-02 Spliet pump handling from manual handler
2025-06-02 Removed not needed log
2025-06-02 Restrucutred GPIO setup
2025-06-23 PCB layout BOOST converter
2025-06-23 Ensure that pump activation is protected by tank verification
2025-06-23 Force low status if tank is empty
2025-06-23 decoupled tank logic and add display handling
2025-06-23 Add pump mutual exclusion for manual case
2025-06-23 Add timer pump mutual exclusion
2025-06-23 PCB design continued -> Top layer mainly routed/ bottom layer GND pour and minor routing left to do + mounting holes
2025-06-24 Finished PCB design
2025-06-25 Finished PCB design / Added Mounting holes position / Plantomatic2000.step generated / Gerber files generated
2025-07-01 Added BOM / Slight adjustments to naming / Boost COUT 47uF not available in 0402 footprint -> ordered 1206 and 22uF 0805 as bacukp
2025-07-02 finised BOM with minor adjustements
2025-09-06 removed gate pull down resistor and re-made erase and boot sequence of ESP32
2025-09-07 Added USB-C PD / Replaced PMIC with TI BMU / Replaced BOOST converter
2025-09-07 Schematic v0.2 done -> check TO DO list
2025-09-13 Added extra LDO for PUMP and Water Sensor / Changed Power fet for USB C PD / Implemented Power Distribution Network and Logic / and various stuff
2025-09-14 Fixed MOSFTE footprints and replaced PFET with a more suitable one
2025-09-15 Footprint for RTC / BMU / USB_C PD are correct
2025-09-16 Added footrpints for inductors and boost convereter
2025-09-18 Checked footprints of diodes, resistors and BJT's
2025-09-21 Schematic annotated, net labes, some values consolidated
2025-10-12 Replaced BOOST converter, previous one didn't support +2A but rather 200 to 300mA, TO DO: re-do schematic annotation for BOOST, re-do BOM for BOOST
2025-10-12 BOM done, except connectors/thermistor/button -> Will re-check BOM before sending to manufacturing
2025-10-13 USB-C and Serial PCB routing done
2025-10-14 PCB desing in progresssss
2025-11-02 Power plane/rearranged connectors
2026-01-24 Hardware for manufacturing v0.2
2026-01-25 Moved the old board to deprecated folder
